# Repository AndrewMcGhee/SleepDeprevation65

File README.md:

# SleepDeprevation65
 First keyboard PCB

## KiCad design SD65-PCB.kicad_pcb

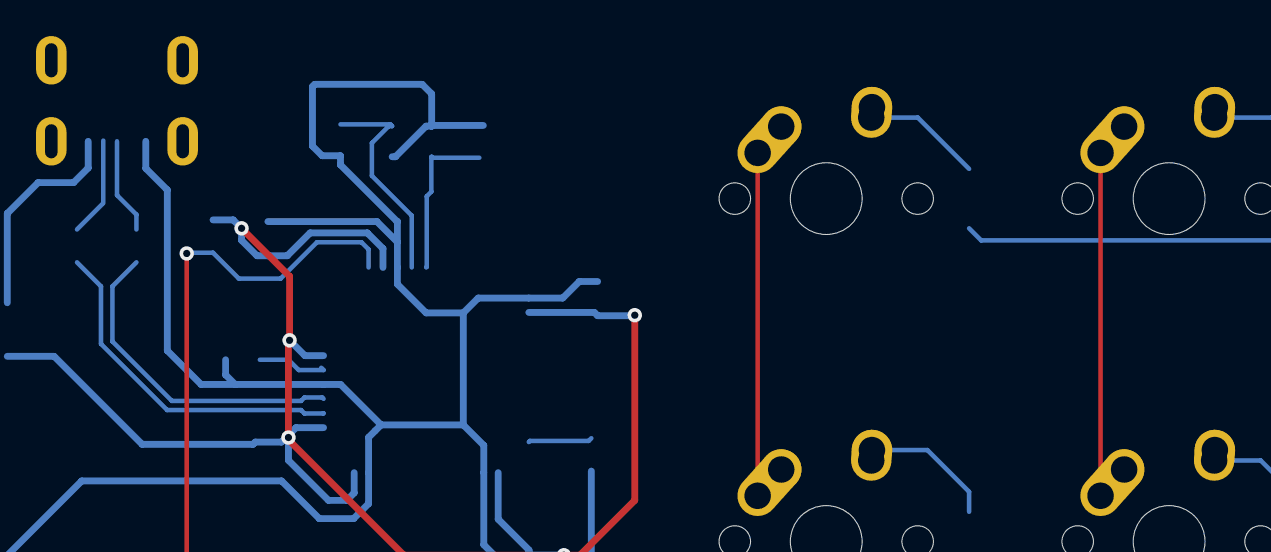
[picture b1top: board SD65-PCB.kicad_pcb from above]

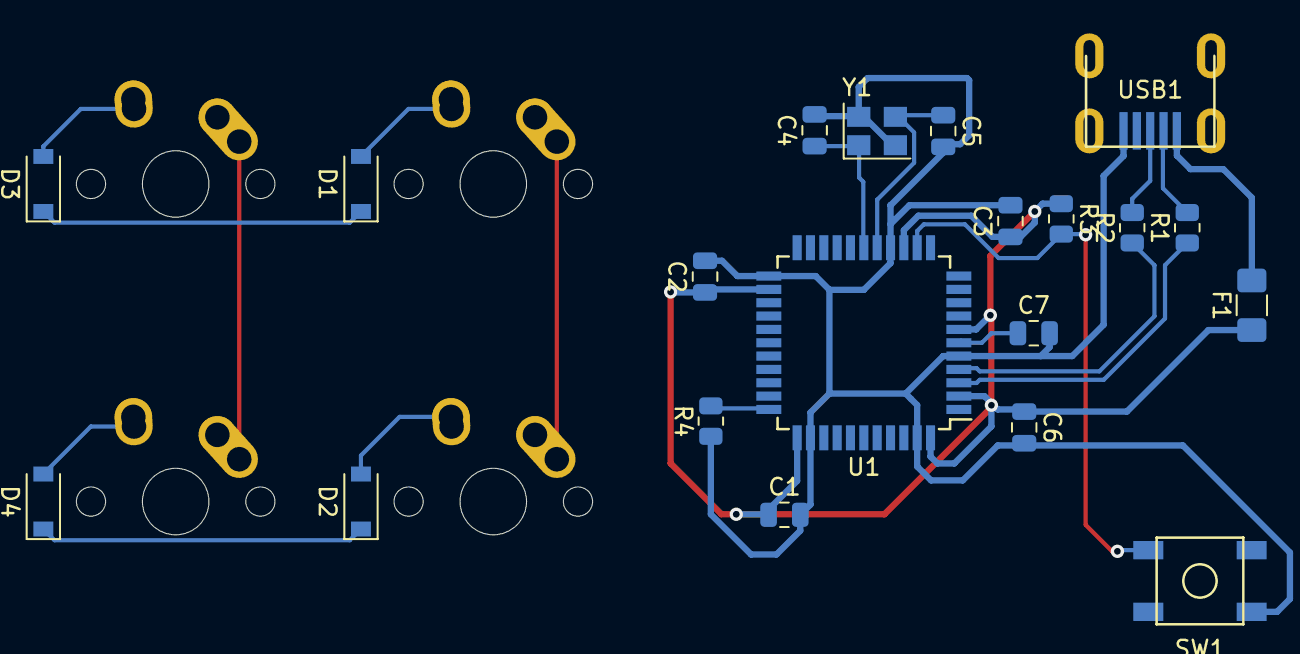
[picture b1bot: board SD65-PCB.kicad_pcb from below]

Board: 2 copper layers, 24 parts (20 on the bottom side), 20 nets.

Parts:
C1, C2, C3: 0.1uF; C_0805_2012Metric
C4, C5: 22pF; C_0805_2012Metric
C6: 10uF; C_0805_2012Metric
C7: 1uF; C_0805_2012Metric
D1, D2, D3, D4: SOD-123; D_SOD-123
F1: 500mA; Fuse_1206_3216Metric_Pad1.42x1.75mm_HandSolder
MX1, MX2, MX3, MX4: MX-NoLED; MX-1U-NoLED
R1, R2: 22; R_0805_2012Metric
R3, R4: 10k; R_0805_2012Metric
SW1: SW_Push; SKQG-1155865
U1: ATmega32U4-AU; TQFP-44_10x10mm_P0.8mm
USB1: Molex-0548190589
Y1: 16MHz; Crystal_SMD_3225-4Pin_3.2x2.5mm

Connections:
+5V: C1.1, C2.1, C3.1, C6.1, F1.1, R3.1, U1.2, U1.7, U1.14, U1.24, U1.34, U1.44
COL0: MX1.1, MX2.1
COL1: MX3.1, MX4.1
D+: R2.2, USB1.3
D-: R1.2, USB1.4
GND: C1.2, C2.2, C3.2, C4.2, C5.2, C6.2, C7.2, R4.1, SW1.1, U1.5, U1.15, U1.23, U1.35, U1.43, USB1.1, Y1.2, Y1.4
unnamed: C4.1, U1.17, Y1.1
unnamed: C5.1, U1.16, Y1.3
unnamed: C7.1, U1.6
unnamed: D1.2, MX1.2
unnamed: D2.2, MX2.2
unnamed: D3.2, MX3.2
unnamed: D4.2, MX4.2
unnamed: R1.1, U1.3
unnamed: R2.1, U1.4
unnamed: R3.2, SW1.2, U1.13
unnamed: R4.2, U1.33
ROW0: D1.1, D3.1
ROW1: D2.1, D4.1
VCC: F1.2, USB1.5

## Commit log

2023-09-22 Initialize Project
2023-09-22 Add Submodules
2023-09-22 Added Part Libraries
2023-09-22 Adding Schematic
2023-09-22 All Parts Placed
    (Only set up for 4 keys right now)
2023-09-22 Most of connections made
